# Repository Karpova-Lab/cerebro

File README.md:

# Cerebro Wireless Optogenetics System v2

Detailed documentation at [https://karpova-lab.github.io/cerebro/](https://karpova-lab.github.io/cerebro/)

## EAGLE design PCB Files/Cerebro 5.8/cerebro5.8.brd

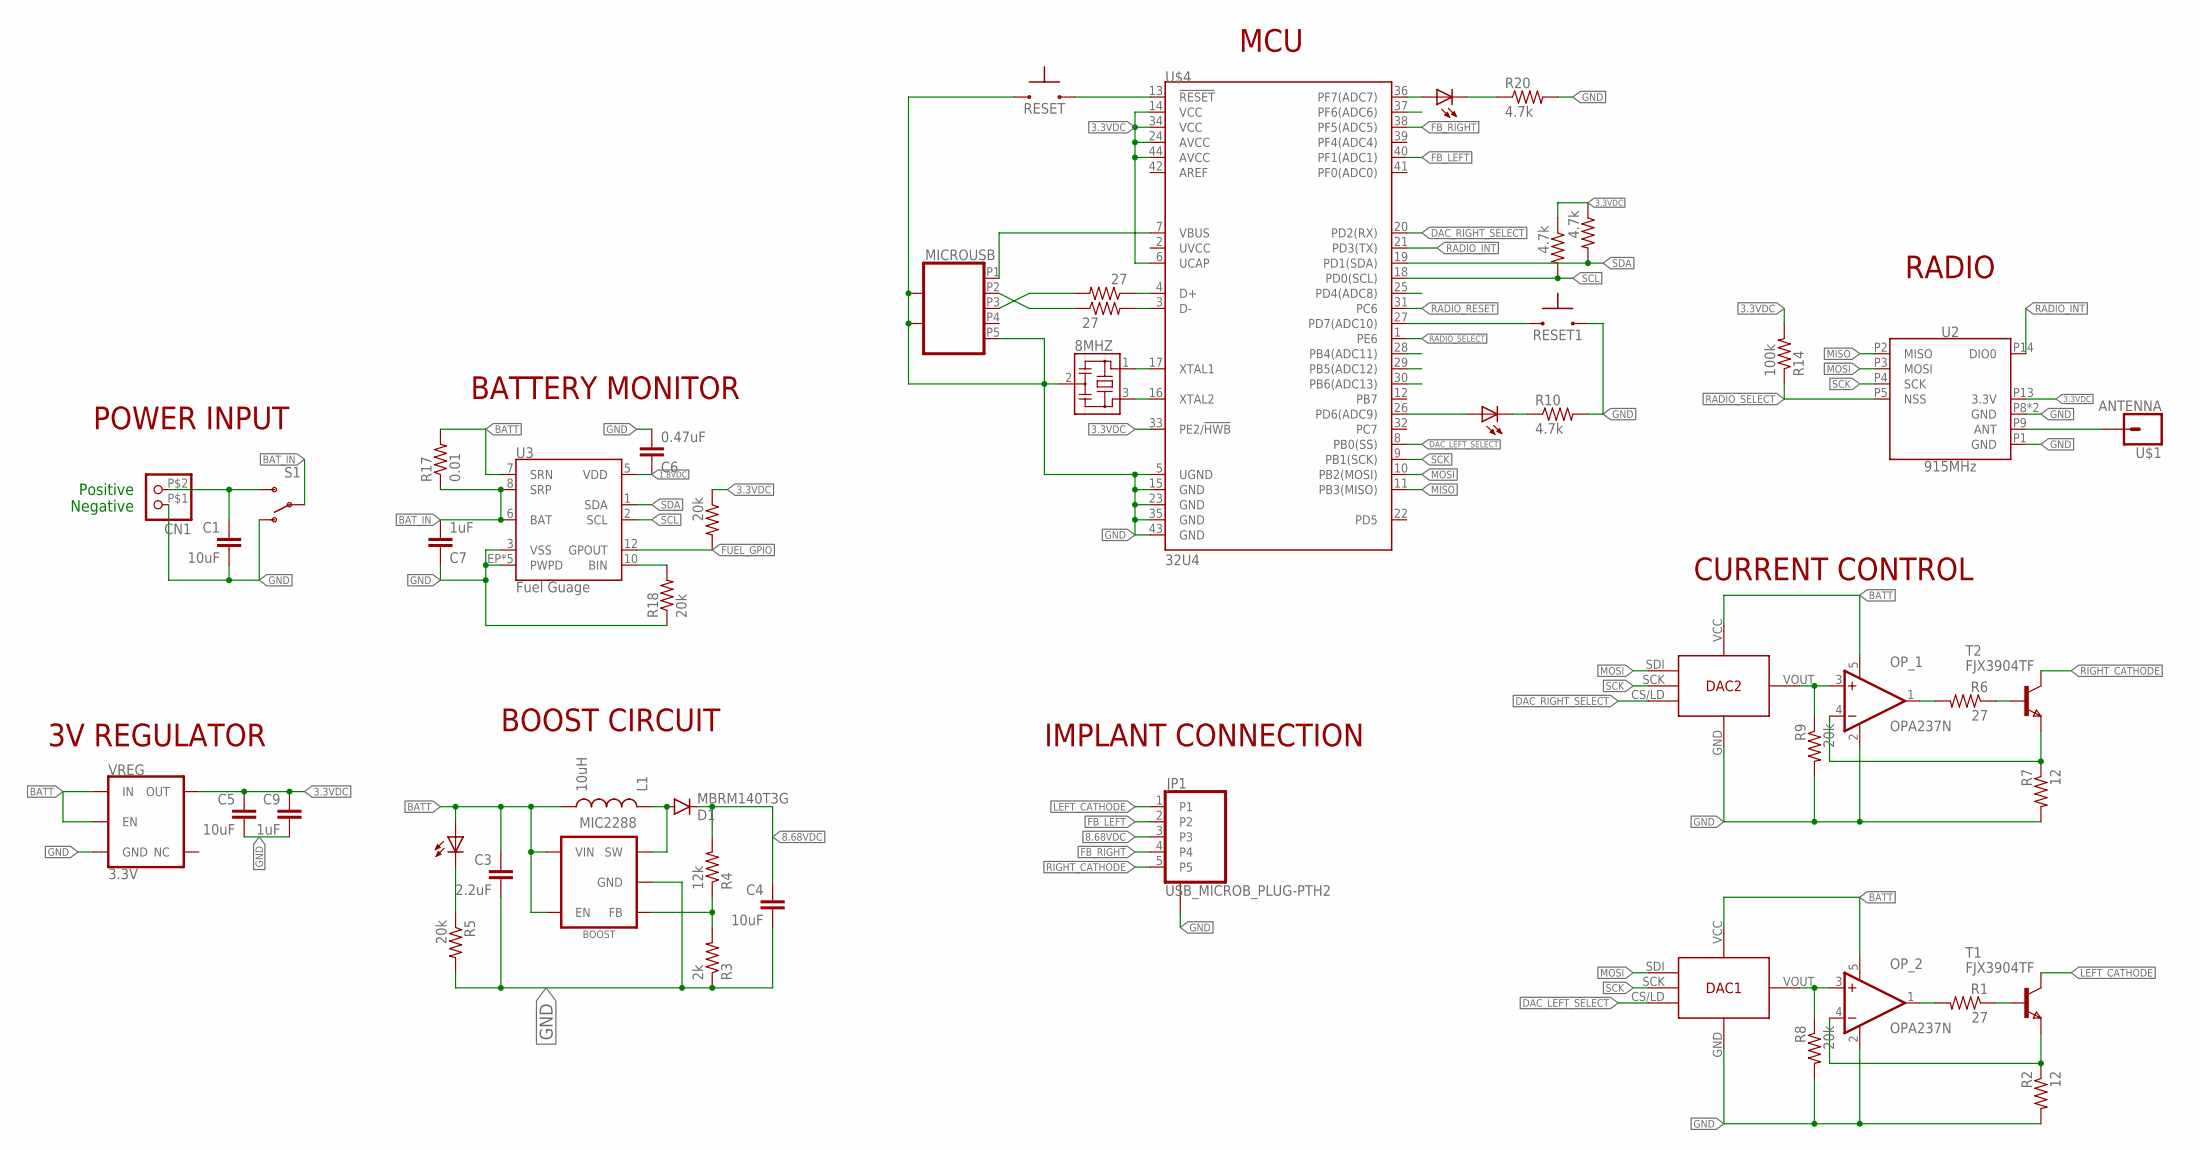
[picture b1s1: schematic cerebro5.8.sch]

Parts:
8MHZ: RESONATOR_CSTCE_V; CSTCE_V
C1, C4, C5: 10uF; 0805
C3: 2.2uF; 0805
C6: 0.47uF; 0805
C7, C9: 1uF; 0805
CN1: JST_2PINMICRO; MICRO_LOCK_2PIN
D1: MBRM140T3G; POWERMITE
DAC1, DAC2: DAC; SC-70
INDICATOR_LED: RED; CHIP-LED0603
INDICATOR_LED1: YLW; CHIP-LED0603
INDICATOR_LED2: GRN; CHIP-LED0603
JP1: USB_MICROB_PLUG-PTH2; MICRO-B-TH
L1: 10uH; 1812
MIC2288: BOOST; SOT23-5
MICROUSB: USB_MICRO_SOCKET_HORZ_REINFORCED; USB_HORZ_REINFORCED_MICRO
OP_1, OP_2: OPA237N; SOT23-5
R1, R6, R12, R13: 27; 0603-RES
R2, R7: 12; 0603-RES
R3: 2k; 0603-RES
R4: 12k; 0805
R5, R8, R9, R18, R19: 20k; 0603-RES
R10, R15, R16, R20: 4.7k; 0603-RES
R14: 100k; 0603-RES
R17: 0.01; 1206
RESET, RESET1: SWITCH-MOMENTARY-NO; SWITCH_MOMENTARY_XS
S1: SWITCH-SPDTREINFORCED_SMD; SWITCH-SPDT-SMD-REINFORCED
T1, T2: FJX3904TF; SOT323
U2: 915MHz; RFM69HCW-XXXS2
U3: Fuel Guage; PDSO-N12
U$1: ANTENNA; 1X01
U$4: 32U4; QFN-44-NOPAD
VREG: 3.3V; SOT23-5

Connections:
1.8VDC: C6.1, U3.5 (VDD)
3.3VDC: C5.1, C9.1, R14.2, R15.1, R16.1, R19.1, U2.P13 (3.3V), U$4.6 (UCAP), U$4.14 (VCC), U$4.24 (AVCC), U$4.33 (PE2/!HWB), U$4.34 (VCC), U$4.44 (AVCC), VREG.5 (OUT)
8.68VDC: C4.1, D1.CATHODE (C), JP1.3, R4.2
BATT: C3.1, DAC1.VCC (VIN), DAC2.VCC (VIN), INDICATOR_LED.A, L1.P$2 (2), L1.P$4 (2), MIC2288.4 (EN), MIC2288.5 (VIN), OP_1.5 (V+), OP_2.5 (V+), R17.2, U3.7 (SRN), VREG.1 (IN), VREG.3 (EN)
BAT_IN: C7.2, R17.1, S1.2, U3.6 (BAT), U3.8 (SRP)
DAC_LEFT_SELECT: DAC1.CS/LD, U$4.8 (PB0(SS))
DAC_RIGHT_SELECT: DAC2.CS/LD, U$4.20 (PD2(RX))
FB_LEFT: JP1.2, U$4.40 (PF1(ADC1))
FB_RIGHT: JP1.4, U$4.38 (PF5(ADC5))
FUEL_GPIO: R19.2, U3.12 (GPOUT)
GND: 8MHZ.2, C1.2, C3.2, C4.2, C5.2, C6.2, C7.1, C9.2, CN1.P$1 (1), DAC1.GND, DAC2.GND, JP1.P$1 (GND_PINS), JP1.P$2 (GND_PINS), MIC2288.2 (GND), MICROUSB.G1, MICROUSB.G2, MICROUSB.P5, MICROUSB.P$1, MICROUSB.P$2, OP_1.2 (V-), OP_2.2 (V-), R2.2, R3.1, R5.2, R7.2, R8.2, R9.2, R10.2, R18.1, R20.2, RESET.P$1 (1), RESET1.P$2 (2), S1.1 (O), U2.P1 (GND), U2.P8 (GND), U2.P10 (GND), U3.3 (VSS), U3.EP (PWPD), U3.EP1 (PWPD), U3.EP2 (PWPD), U3.EP3 (PWPD), U3.EP4 (PWPD), U$4.5 (UGND), U$4.15 (GND), U$4.23 (GND), U$4.35 (GND), U$4.43 (GND), VREG.2 (GND)
LEFT_CATHODE: JP1.1, T1.1 (C)
MISO: U2.P2 (MISO), U$4.11 (PB3(MISO))
MOSI: DAC1.SDI, DAC2.SDI, U2.P3 (MOSI), U$4.10 (PB2(MOSI))
unnamed: DAC2.VOUT, OP_1.3 (+IN), R9.1
unnamed: OP_1.4 (-IN), R7.1, T2.3 (E)
unnamed: DAC1.VOUT, OP_2.3 (+IN), R8.1
unnamed: C1.1, CN1.P$2 (2), S1.3 (S)
unnamed: OP_1.1 (OUT), R6.2
unnamed: OP_2.4 (-IN), R2.1, T1.3 (E)
unnamed: R6.1, T2.2 (B)
unnamed: INDICATOR_LED.C, R5.1
unnamed: OP_2.1 (OUT), R1.2
unnamed: MIC2288.3 (FB), R3.2, R4.1
unnamed: R1.1, T1.2 (B)
unnamed: 8MHZ.1, U$4.17 (XTAL1)
unnamed: 8MHZ.3, U$4.16 (XTAL2)
unnamed: MICROUSB.P1, U$4.7 (VBUS)
unnamed: D1.ANODE (A), L1.P$1 (1), L1.P$3 (1), MIC2288.1 (SW)
unnamed: R12.1, U$4.4 (D+)
unnamed: R13.2, U$4.3 (D-)
unnamed: MICROUSB.P3, R12.2
unnamed: MICROUSB.P2, R13.1
unnamed: INDICATOR_LED2.C, R10.1
unnamed: RESET1.P$1 (1), U$4.27 (PD7(ADC10))
unnamed: U2.P9 (ANT), U$1.1
unnamed: INDICATOR_LED1.C, R20.1
unnamed: INDICATOR_LED1.A, U$4.36 (PF7(ADC7))
unnamed: R18.2, U3.10 (BIN)
unnamed: INDICATOR_LED2.A, U$4.26 (PD6(ADC9))
RADIO_INT: U2.P14 (DIO0), U$4.21 (PD3(TX))
RADIO_RESET: U$4.31 (PC6)
RADIO_SELECT: R14.1, U2.P5 (NSS), U$4.1 (PE6)
RESET: RESET.P$2 (2), U$4.13 (!RESET)
RIGHT_CATHODE: JP1.5, T2.1 (C)
SCK: DAC1.SCK, DAC2.SCK, U2.P4 (SCK), U$4.9 (PB1(SCK))
SCL: R15.2, U3.2 (SCL), U$4.18 (PD0(SCL))
SDA: R16.2, U3.1 (SDA), U$4.19 (PD1(SDA))

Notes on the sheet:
Positive
Negative
BOOST CIRCUIT
CURRENT CONTROL
RADIO
3V REGULATOR
BATTERY MONITOR
POWER INPUT
IMPLANT CONNECTION
MCU

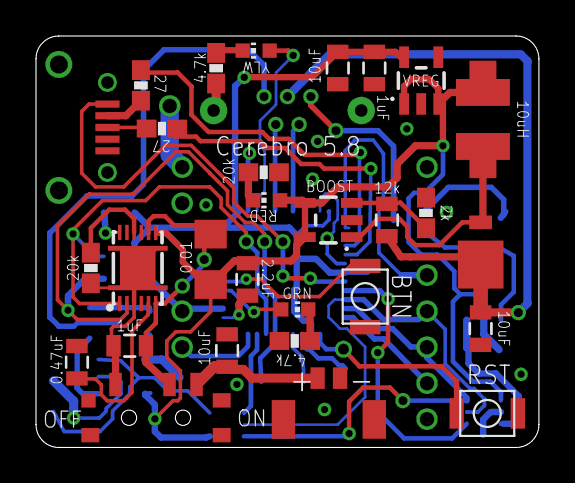
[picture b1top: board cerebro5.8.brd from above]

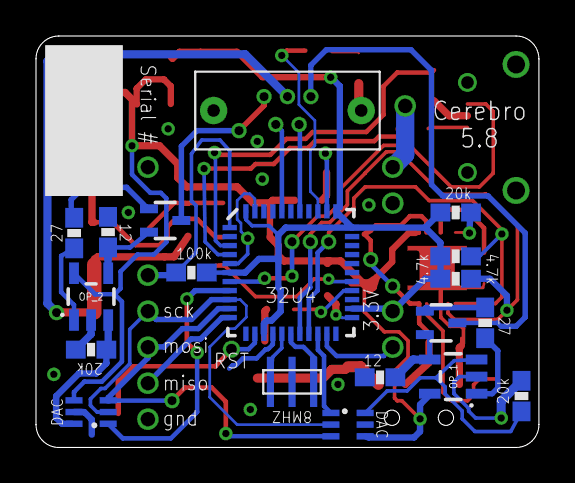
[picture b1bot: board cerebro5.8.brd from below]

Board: 2 copper layers, 27.9 x 22.9 mm, 50 parts (19 on the bottom side), 47 nets.

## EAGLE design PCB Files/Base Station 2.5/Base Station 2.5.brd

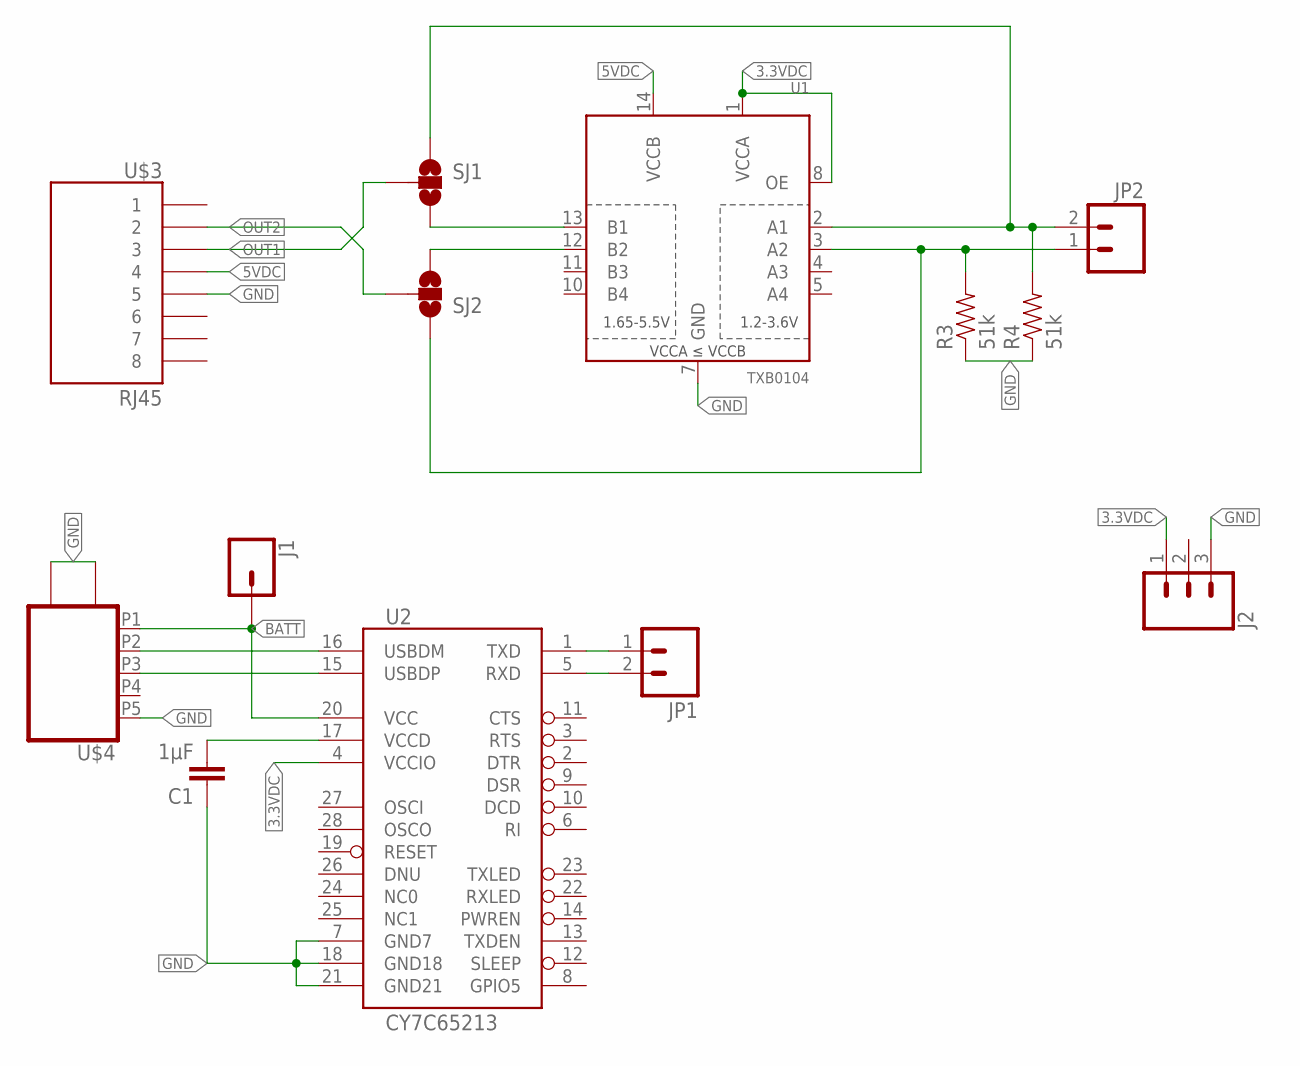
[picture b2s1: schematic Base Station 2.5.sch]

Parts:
C1: 1µF; 0603
J1: CONN_01PTH_NO_SILK_YES_STOP; 1X01_NO_SILK
J2: CONN_031X03_NO_SILK; 1X03_NO_SILK
JP1, JP2: M021X02_NO_SILK; 1X02_NO_SILK
R3, R4: 51k; 0805
SJ1, SJ2: SOLDERJUMPER_2WAYPASTE2&3; SJ_3_PASTE2&3
U1: TXB0104; TSSOP14
U2: CY7C65213; SSOP28DB
U$3: RJ45; RJ45-8
U$4: USB_MICRO_SOCKET_HORZ_REINFORCED; USB_HORZ_REINFORCED_MICRO

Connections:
3.3VDC: J2.1, U1.1 (VCCA), U1.8 (OE), U2.4 (VCCIO)
5VDC: U1.14 (VCCB), U$3.4
BATT: J1.1, U2.20 (VCC), U$4.P1
GND: C1.1, J2.3, R3.1, R4.1, U1.7 (GND), U2.7 (GND7), U2.18 (GND18), U2.21 (GND21), U$3.5, U$4.G1, U$4.G2, U$4.P5, U$4.P$1, U$4.P$2
unnamed: JP1.1, U2.1 (TXD)
unnamed: JP1.2, U2.5 (RXD)
unnamed: U2.15 (USBDP), U$4.P3
unnamed: U2.16 (USBDM), U$4.P2
unnamed: C1.2, U2.17 (VCCD)
unnamed: JP2.2, R4.2, SJ1.1, U1.2 (A1)
unnamed: JP2.1, R3.2, SJ2.1, U1.3 (A2)
unnamed: SJ2.3, U1.12 (B2)
unnamed: SJ1.3, U1.13 (B1)
NC1: U2.25 (NC1)
OUT1: SJ1.2, U$3.3
OUT2: SJ2.2, U$3.2

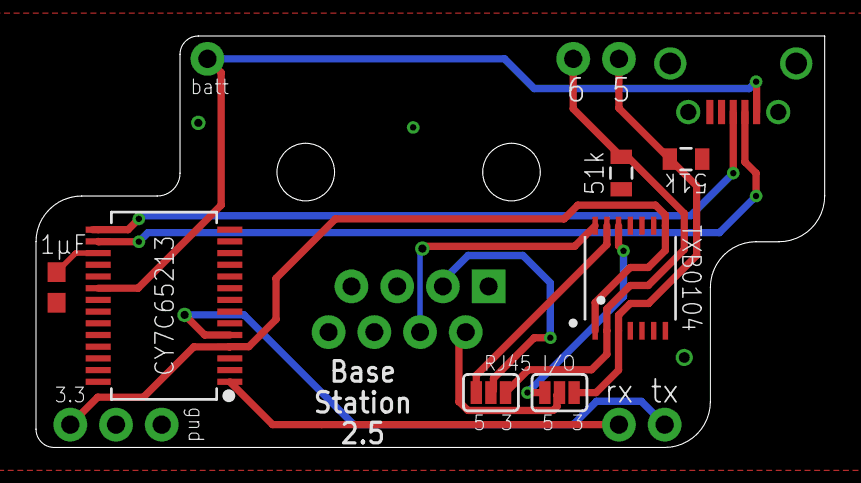
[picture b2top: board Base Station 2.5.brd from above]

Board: 2 copper layers, 43.8 x 22.9 mm, 13 parts (0 on the bottom side), 15 nets.

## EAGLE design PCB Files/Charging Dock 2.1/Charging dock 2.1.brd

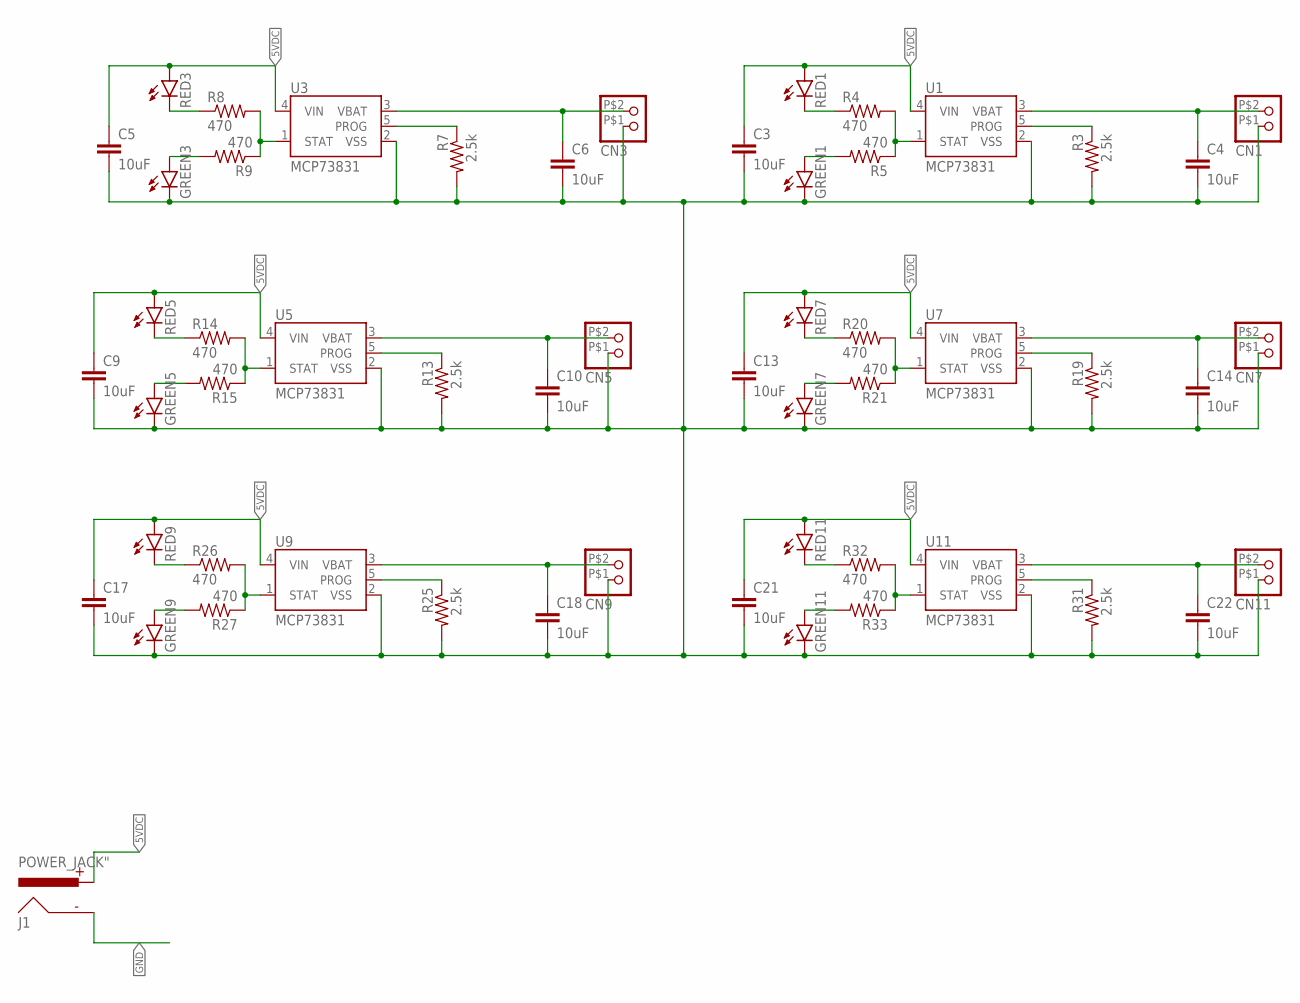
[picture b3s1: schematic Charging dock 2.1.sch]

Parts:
C3, C4, C5, C6, C9, C10, C13, C14, C17, C18, C21, C22: 10uF; 0805
CN1, CN3, CN5, CN7, CN9, CN11: JST_2PINMICRO; MICRO_LOCK_2PIN
GREEN1, GREEN3, GREEN5, GREEN7, GREEN9, GREEN11: LED3MM
J1: POWER_JACK"; BARREL_CONN
R3, R7, R13, R19, R25, R31: 2.5k; 0805
R4, R5, R8, R9, R14, R15, R20, R21, R26, R27, R32, R33: 470; 0805
RED1, RED3, RED5, RED7, RED9, RED11: LED3MM
U1, U3, U5, U7, U9, U11: MCP73831; SOT23-5

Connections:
5VDC: C3.1, C5.1, C9.1, C13.1, C17.1, C21.1, J1.PWR, RED1.A, RED3.A, RED5.A, RED7.A, RED9.A, RED11.A, U1.4 (VIN), U3.4 (VIN), U5.4 (VIN), U7.4 (VIN), U9.4 (VIN), U11.4 (VIN)
GND: C3.2, C4.2, C5.2, C6.2, C9.2, C10.2, C13.2, C14.2, C17.2, C18.2, C21.2, C22.2, CN1.P$1 (1), CN3.P$1 (1), CN5.P$1 (1), CN7.P$1 (1), CN9.P$1 (1), CN11.P$1 (1), GREEN1.K (C), GREEN3.K (C), GREEN5.K (C), GREEN7.K (C), GREEN9.K (C), GREEN11.K (C), J1.GND, R3.2, R7.2, R13.2, R19.2, R25.2, R31.2, U1.2 (VSS), U3.2 (VSS), U5.2 (VSS), U7.2 (VSS), U9.2 (VSS), U11.2 (VSS)
unnamed: R3.1, U1.5 (PROG)
unnamed: R4.1, RED1.K (C)
unnamed: R4.2, R5.1, U1.1 (STAT)
unnamed: GREEN1.A, R5.2
unnamed: R7.1, U3.5 (PROG)
unnamed: R8.1, RED3.K (C)
unnamed: R8.2, R9.1, U3.1 (STAT)
unnamed: GREEN3.A, R9.2
unnamed: R13.1, U5.5 (PROG)
unnamed: R14.1, RED5.K (C)
unnamed: R14.2, R15.1, U5.1 (STAT)
unnamed: GREEN5.A, R15.2
unnamed: R19.1, U7.5 (PROG)
unnamed: R20.1, RED7.K (C)
unnamed: R20.2, R21.1, U7.1 (STAT)
unnamed: GREEN7.A, R21.2
unnamed: R25.1, U9.5 (PROG)
unnamed: R26.1, RED9.K (C)
unnamed: R26.2, R27.1, U9.1 (STAT)
unnamed: GREEN9.A, R27.2
unnamed: R31.1, U11.5 (PROG)
unnamed: R32.1, RED11.K (C)
unnamed: R32.2, R33.1, U11.1 (STAT)
unnamed: GREEN11.A, R33.2
NW_CHARGE1: C4.1, CN1.P$2 (2), U1.3 (VBAT)
NW_CHARGE3: C6.1, CN3.P$2 (2), U3.3 (VBAT)
NW_CHARGE5: C10.1, CN5.P$2 (2), U5.3 (VBAT)
NW_CHARGE7: C14.1, CN7.P$2 (2), U7.3 (VBAT)
NW_CHARGE9: C18.1, CN9.P$2 (2), U9.3 (VBAT)
NW_CHARGE11: C22.1, CN11.P$2 (2), U11.3 (VBAT)

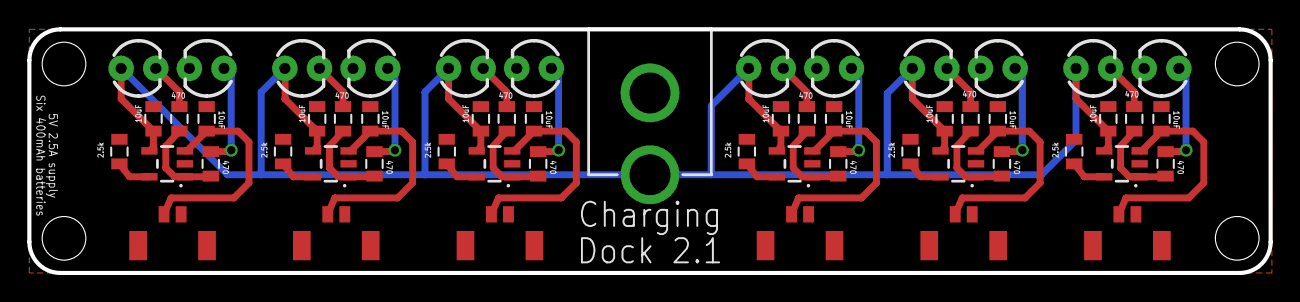
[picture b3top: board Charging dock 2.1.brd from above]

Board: 2 copper layers, 91.0 x 17.9 mm, 55 parts (0 on the bottom side), 32 nets.

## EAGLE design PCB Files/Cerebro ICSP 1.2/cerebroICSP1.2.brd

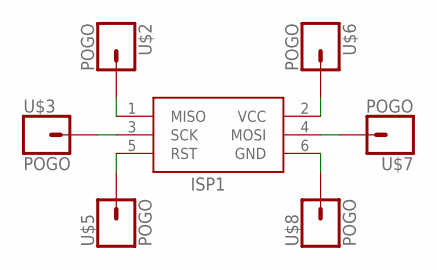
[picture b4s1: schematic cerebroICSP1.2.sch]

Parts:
ISP1: AVRISP-BOX
U$2, U$3, U$5, U$6, U$7, U$8: POGO

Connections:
unnamed: ISP1.1 (MISO), U$2.P$1
unnamed: ISP1.3 (SCK), U$3.P$1
unnamed: ISP1.5 (RST), U$5.P$1
unnamed: ISP1.2 (VCC), U$6.P$1
unnamed: ISP1.4 (MOSI), U$7.P$1
unnamed: ISP1.6 (GND), U$8.P$1

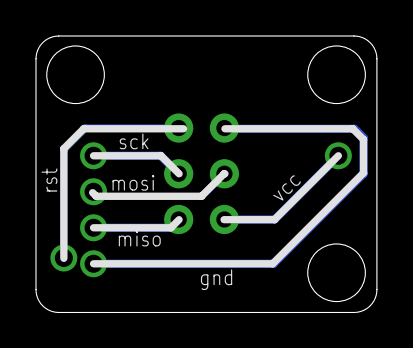
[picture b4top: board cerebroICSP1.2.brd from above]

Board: 2 copper layers, 18.9 x 15.4 mm, 7 parts (1 on the bottom side), 6 nets.

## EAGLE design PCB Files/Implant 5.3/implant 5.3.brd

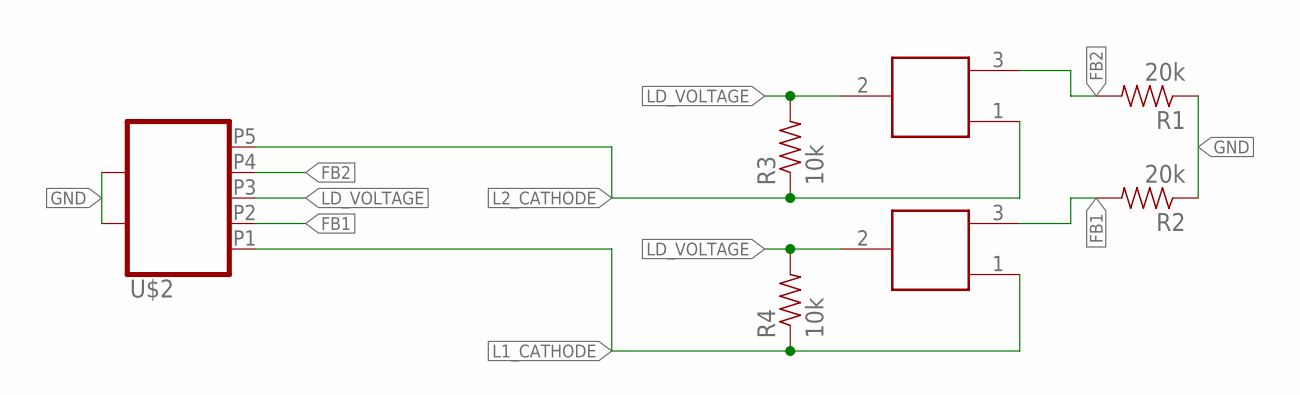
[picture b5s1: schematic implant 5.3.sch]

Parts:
R1, R2: 20k; 0805
R3, R4: 10k; 0805
U$2: USB_MICRO_SOCKET_VERT; USB_VERT_MICRO_SMD
U$6, U$7: LASERDIODE5.6MM; LASERDIODE_5.6

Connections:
FB1: R2.2, U$2.P2, U$6.3
FB2: R1.2, U$2.P4, U$7.3
GND: R1.1, R2.1, U$2.P$1, U$2.P$2, U$2.P$3
L1_CATHODE: R4.1, U$2.P1, U$6.1
L2_CATHODE: R3.1, U$2.P5, U$7.1
LD_VOLTAGE: R3.2, R4.2, U$2.P3, U$6.2, U$7.2

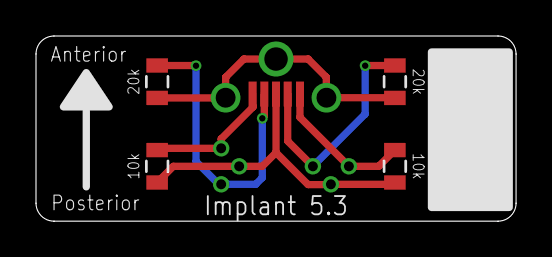
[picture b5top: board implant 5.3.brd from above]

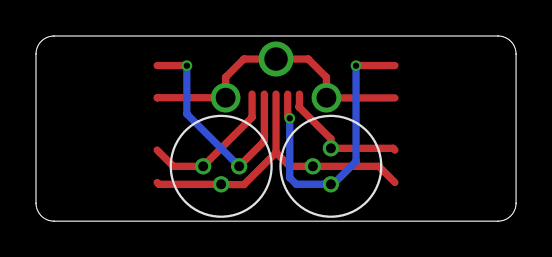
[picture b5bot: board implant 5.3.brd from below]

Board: 2 copper layers, 26.7 x 10.3 mm, 7 parts (2 on the bottom side), 6 nets.

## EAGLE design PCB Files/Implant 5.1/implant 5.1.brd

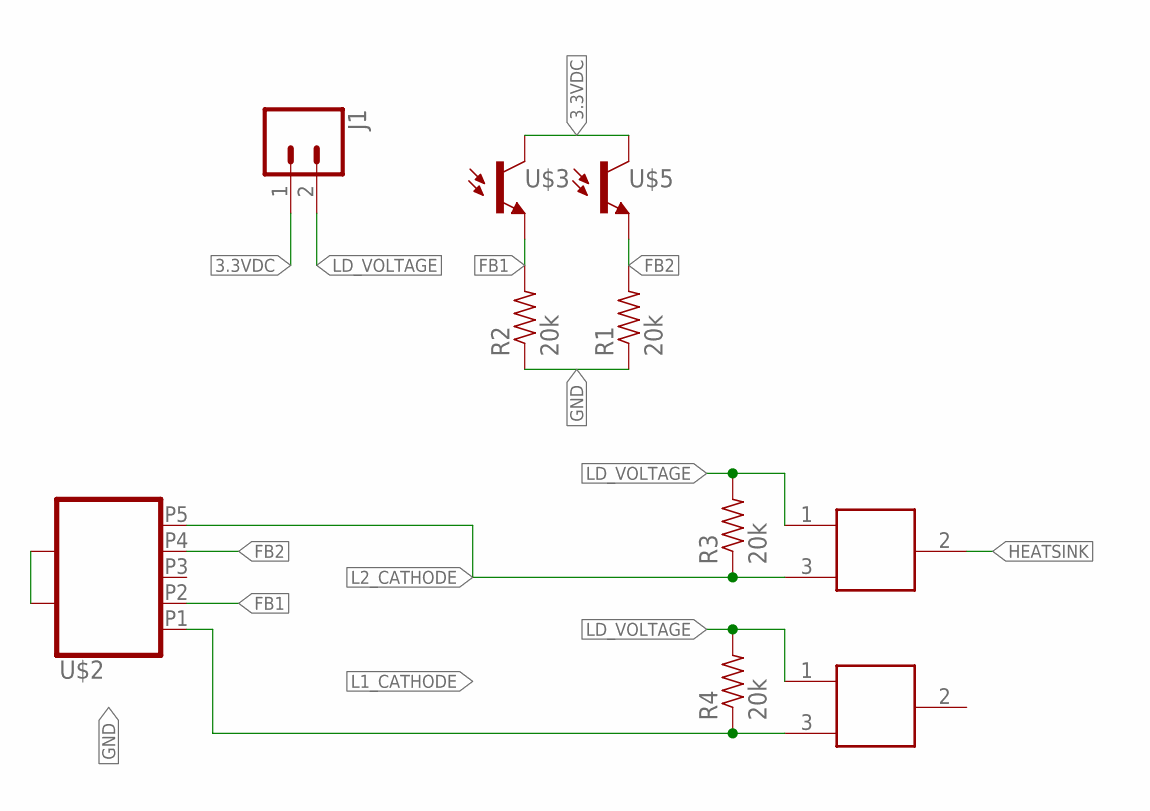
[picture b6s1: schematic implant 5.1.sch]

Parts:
J1: CONN_02; 1X02
R1, R2, R3, R4: 20k; 0805
U$1, U$4: LASERDIODE3.8MM; LASERDIODE_3.8
U$2: USB_MICRO_SOCKET_VERT; USB_VERT_MICRO_SMD
U$3, U$5: AMBIENT-LIGHT-SENSOR; PHOTO_PACK

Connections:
3.3VDC: J1.1, U$3.COLLECTOR (C), U$5.COLLECTOR (C)
FB1: R2.2, U$2.P2, U$3.EMITTER (E)
FB2: R1.2, U$2.P4, U$5.EMITTER (E)
GND: R1.1, R2.1, U$2.P$1, U$2.P$2, U$2.P$3
HEATSINK: U$4.2
L1_CATHODE: R4.1, U$1.3, U$2.P1
L2_CATHODE: R3.1, U$2.P5, U$4.3
LD_VOLTAGE: J1.2, R3.2, R4.2, U$1.1, U$4.1

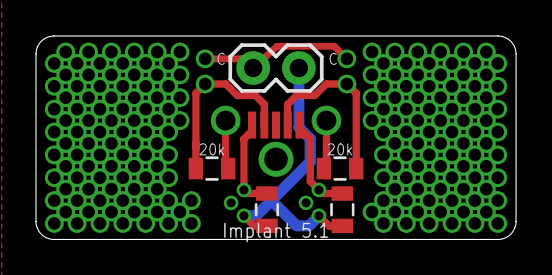
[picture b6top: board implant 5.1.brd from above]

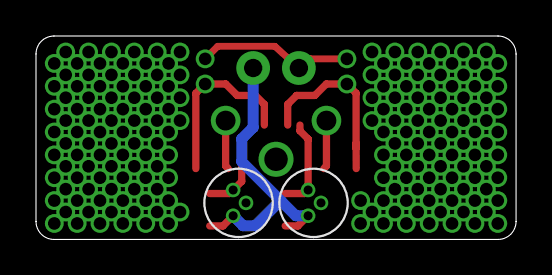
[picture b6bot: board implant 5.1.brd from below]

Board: 2 copper layers, 26.7 x 11.3 mm, 10 parts (2 on the bottom side), 7 nets.

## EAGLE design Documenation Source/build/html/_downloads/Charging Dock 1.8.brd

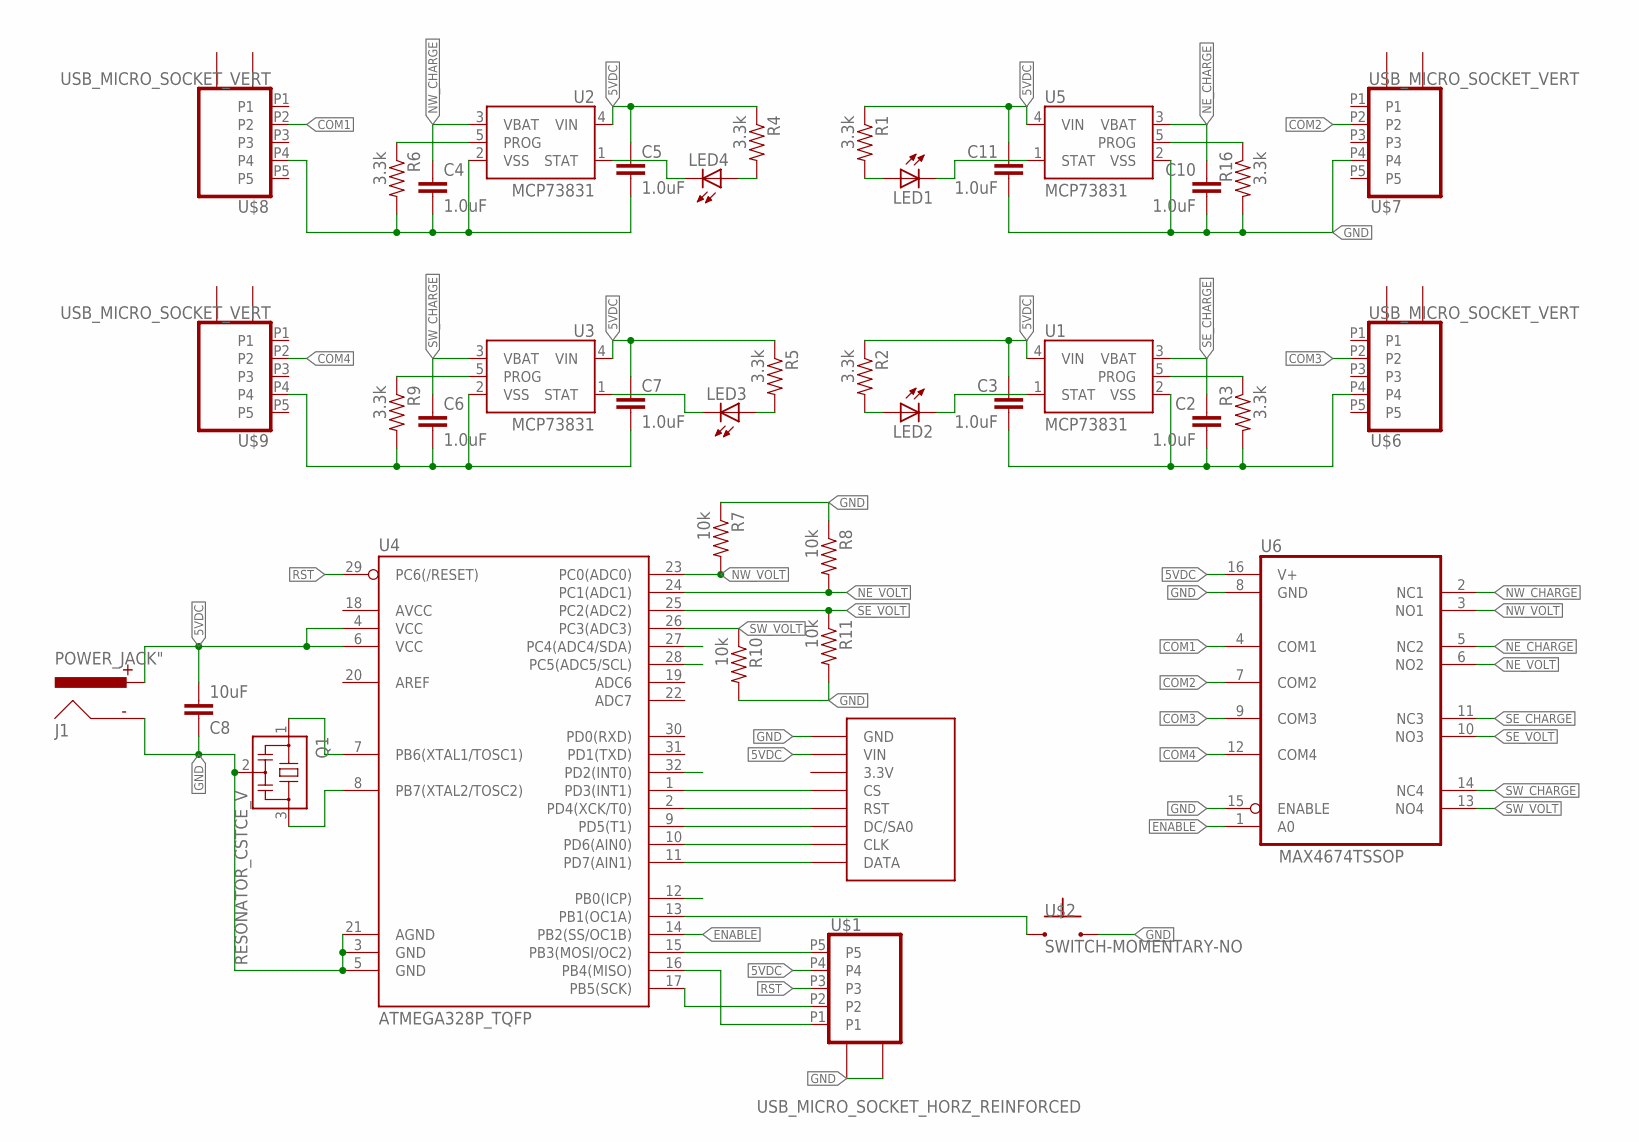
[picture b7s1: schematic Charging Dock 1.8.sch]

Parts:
C2, C3, C4, C5, C6, C7, C10, C11: 1.0uF; 0805-CAP
C8: 10uF; 0805-CAP
J1: POWER_JACK"; BARREL_CONN
LED1, LED2, LED3, LED4: LEDCHIPLED_0805; CHIPLED_0805
Q1: RESONATOR_CSTCE_V; CSTCE_V
R1, R2, R3, R4, R5, R6, R9, R16: 3.3k; 0805
R7, R8, R10, R11: 10k; 0805
U1, U2, U3, U5: MCP73831; SOT23-5
U4: ATMEGA328P_TQFP; TQFP32-08
U6: MAX4674TSSOP; TSSOP16
U$1: USB_MICRO_SOCKET_HORZ_REINFORCED; USB_HORZ_REINFORCED_MICRO
U$2: SWITCH-MOMENTARY-NO; SWITCH_MOMENTARY_XS
U$6, U$7, U$8, U$9: USB_MICRO_SOCKET_VERT; USB_VERT_MICRO_SMD
U$10: OLED_DISPLAY

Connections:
3.3V: U$10.3V3 (3.3V)
5VDC: C3.1, C5.1, C7.1, C8.2, C11.1, J1.PWR, R1.1, R2.1, R4.1, R5.1, U1.4 (VIN), U2.4 (VIN), U3.4 (VIN), U4.4 (VCC), U4.6 (VCC), U5.4 (VIN), U6.16 (V+), U$1.P4, U$10.VIN
COM1: U6.4 (COM1), U$8.P2
COM2: U6.7 (COM2), U$7.P2
COM3: U6.9 (COM3), U$6.P2
COM4: U6.12 (COM4), U$9.P2
ENABLE: U4.14 (PB2(SS/OC1B)), U6.1 (A0)
GND: C2.2, C3.2, C4.2, C5.2, C6.2, C7.2, C8.1, C10.2, C11.2, J1.GND, Q1.2, R3.2, R6.2, R7.1, R8.1, R9.2, R10.2, R11.2, R16.2, U1.2 (VSS), U2.2 (VSS), U3.2 (VSS), U4.3 (GND), U4.5 (GND), U4.21 (AGND), U5.2 (VSS), U6.8 (GND), U6.15 (ENABLE), U$1.G1, U$1.G2, U$1.P$1, U$1.P$2, U$2.P$2 (2), U$6.P4, U$7.P4, U$8.P4, U$9.P4, U$10.GND
unnamed: LED1.A, R1.2
unnamed: R9.1, U3.5 (PROG)
unnamed: LED3.A, R5.2
unnamed: LED2.C, U1.1 (STAT)
unnamed: LED4.A, R4.2
unnamed: LED2.A, R2.2
unnamed: R6.1, U2.5 (PROG)
unnamed: LED4.C, U2.1 (STAT)
unnamed: U4.15 (PB3(MOSI/OC2)), U$1.P5
unnamed: U4.17 (PB5(SCK)), U$1.P2
unnamed: U4.16 (PB4(MISO)), U$1.P1
unnamed: R16.1, U5.5 (PROG)
unnamed: U4.1 (PD3(INT1)), U$10.CS
unnamed: LED3.C, U3.1 (STAT)
unnamed: Q1.3, U4.8 (PB7(XTAL2/TOSC2))
unnamed: Q1.1, U4.7 (PB6(XTAL1/TOSC1))
unnamed: U4.2 (PD4(XCK/T0)), U$10.RST
unnamed: U4.9 (PD5(T1)), U$10.DC (DC/SA0)
unnamed: U4.10 (PD6(AIN0)), U$10.CLK
unnamed: U4.11 (PD7(AIN1)), U$10.DATA
unnamed: R3.1, U1.5 (PROG)
unnamed: U4.13 (PB1(OC1A)), U$2.P$1 (1)
unnamed: LED1.C, U5.1 (STAT)
NE_CHARGE: C10.1, U5.3 (VBAT), U6.5 (NC2)
NE_VOLT: R8.2, U4.24 (PC1(ADC1)), U6.6 (NO2)
NW_CHARGE: C4.1, U2.3 (VBAT), U6.2 (NC1)
NW_VOLT: R7.2, U4.23 (PC0(ADC0)), U6.3 (NO1)
RST: U4.29 (PC6(/RESET)), U$1.P3
SE_CHARGE: C2.1, U1.3 (VBAT), U6.11 (NC3)
SE_VOLT: R11.1, U4.25 (PC2(ADC2)), U6.10 (NO3)
SW_CHARGE: C6.1, U3.3 (VBAT), U6.14 (NC4)
SW_VOLT: R10.1, U4.26 (PC3(ADC3)), U6.13 (NO4)

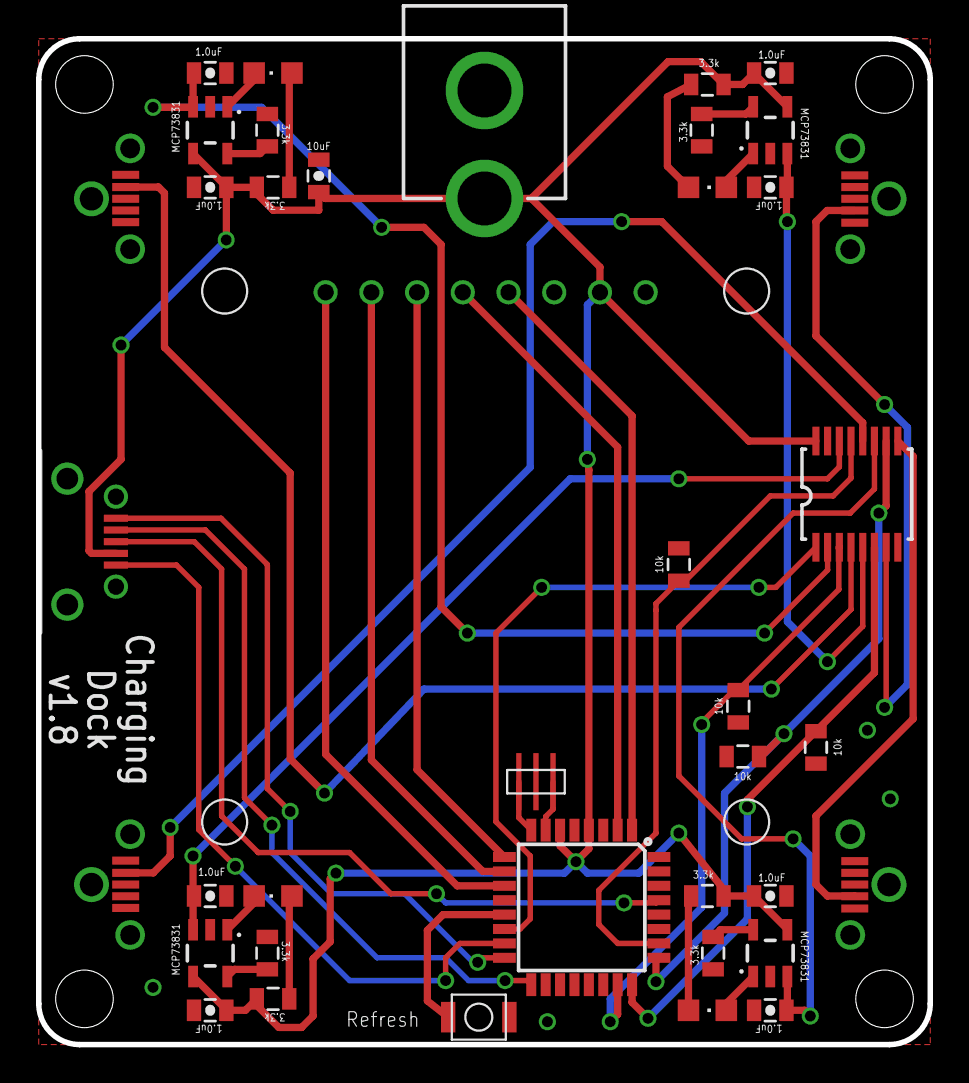
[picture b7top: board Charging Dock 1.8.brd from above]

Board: 2 copper layers, 49.5 x 55.9 mm, 41 parts (1 on the bottom side), 39 nets.

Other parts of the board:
U$15: OSHW-LOGO-M

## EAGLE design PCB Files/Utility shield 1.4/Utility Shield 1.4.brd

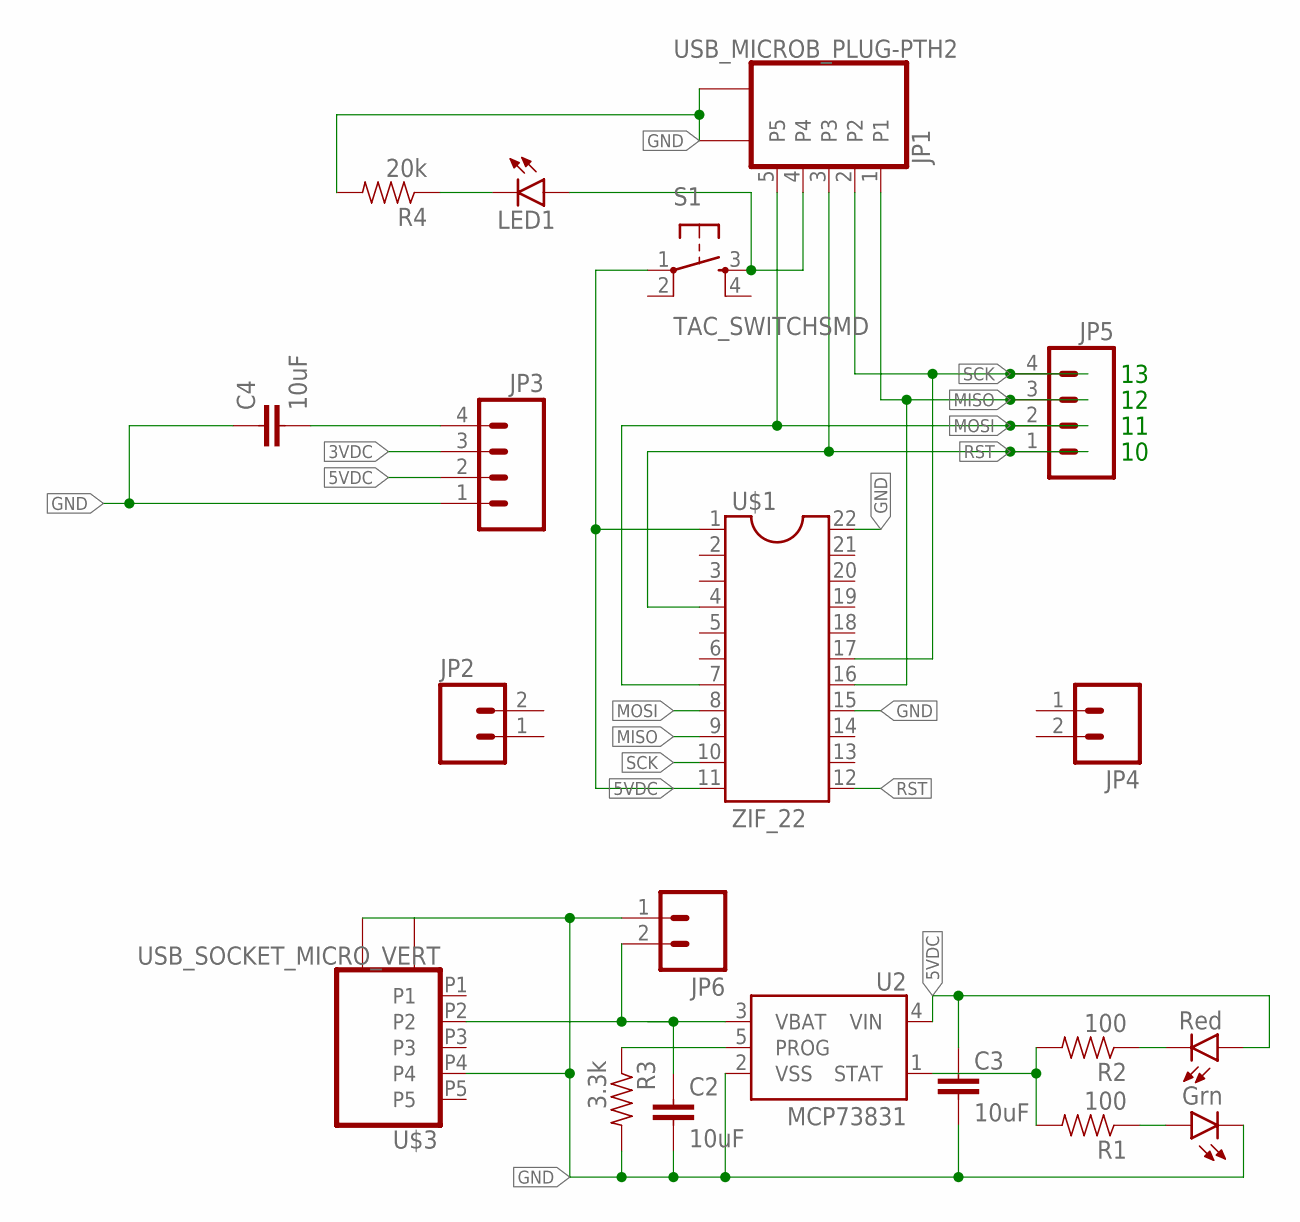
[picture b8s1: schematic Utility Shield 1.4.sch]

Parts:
C2, C3, C4: 10uF; 0805-CAP
JP1: USB_MICROB_PLUG-PTH2; MICRO-B-TH
JP2, JP4: M02PTH; 1X02
JP3, JP5: M04PTH; 1X04
JP6: M02-JST-2-PTH-NO_SILK; JST-2-PTH-NS
LED1: LED0603; LED-0603
R1, R2: 100; 0805
R3: 3.3k; 0805
R4: 20k; 0805
S1: TAC_SWITCHSMD; TACTILE-SWITCH-SMD
U2: MCP73831; SOT23-5
U$1: ZIF_22
U$2: LED_DUAL
U$3: USB_SOCKET_MICRO_VERT; USB_VERT_MICRO_SMD

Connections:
3VDC: JP3.3
5VDC: C3.1, JP3.2, S1.1, U2.4 (VIN), U$1.1, U$1.11, U$2.RA
GND: C2.2, C3.2, C4.1, JP1.P$1, JP1.P$2, JP3.1, JP6.1, R3.2, R4.2, U2.2 (VSS), U$1.15, U$1.22, U$2.GC, U$3.P4, U$3.P$1, U$3.P$2, U$3.P$3
MISO: JP1.1, JP5.3, U$1.9, U$1.16
MOSI: JP1.5, JP5.2, U$1.7, U$1.8
unnamed: C4.2, JP3.4
unnamed: LED1.C, R4.1
unnamed: R1.2, R2.2, U2.1 (STAT)
unnamed: R1.1, U$2.GA
unnamed: R2.1, U$2.RC
unnamed: R3.1, U2.5 (PROG)
unnamed: JP1.4, LED1.A, S1.3
unnamed: C2.1, JP6.2, U2.3 (VBAT), U$3.P2
RST: JP1.3, JP5.1, U$1.4, U$1.12
SCK: JP1.2, JP5.4, U$1.10, U$1.17

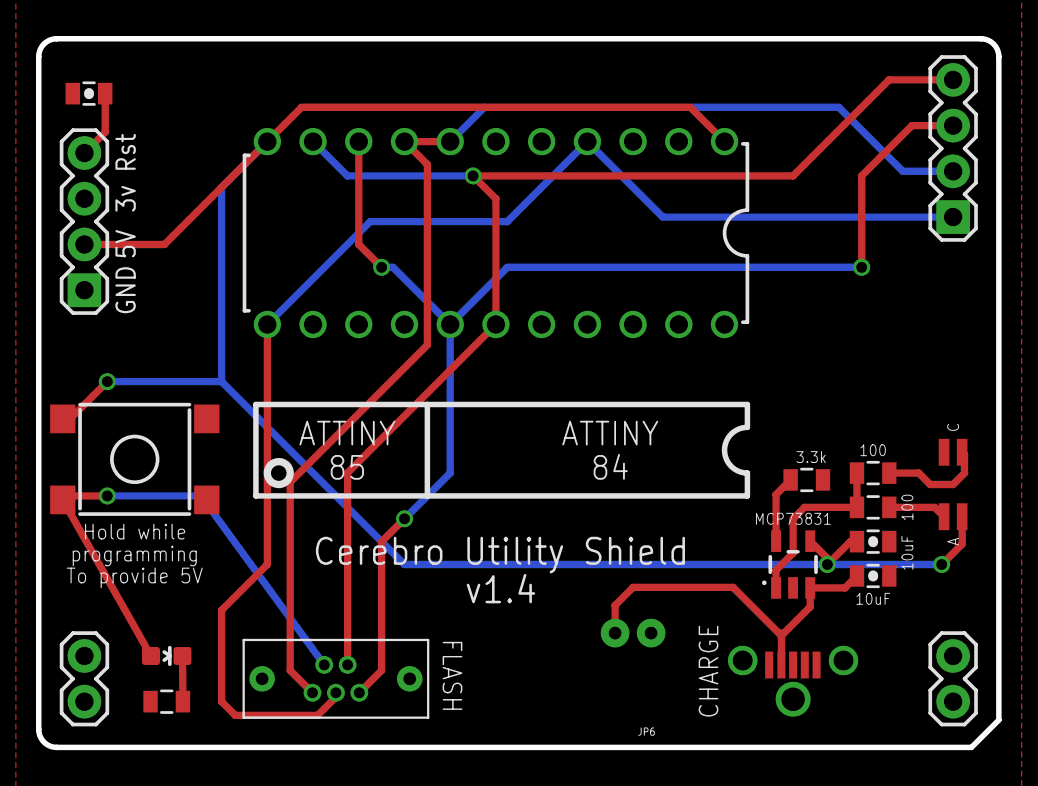
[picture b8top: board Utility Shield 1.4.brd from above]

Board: 2 copper layers, 53.3 x 39.4 mm, 19 parts (1 on the bottom side), 14 nets.

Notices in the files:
parts and their libraries:
SparkFun-PowerIC: Licensing: Creative Commons ShareAlike 4.0 International - https://creativecommons.org/licenses/by-sa/4.0
